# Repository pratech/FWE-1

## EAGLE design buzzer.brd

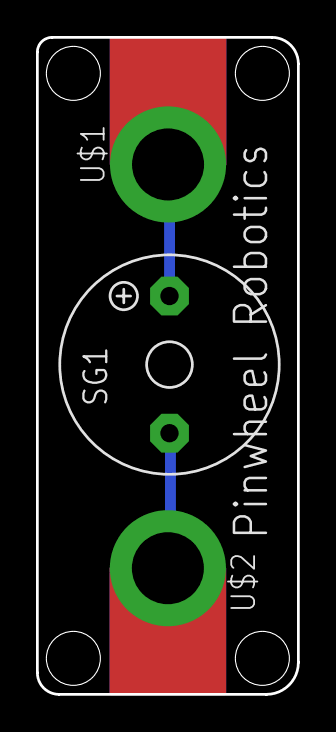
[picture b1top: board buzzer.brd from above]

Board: 2 copper layers, 14.5 x 36.5 mm, 3 parts (0 on the bottom side), 2 nets.

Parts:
SG1: F/TMB
U$1, U$2: MICROBIT_PAD

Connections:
unnamed: SG1.+, U$1.PAD
unnamed: SG1.-, U$2.PAD

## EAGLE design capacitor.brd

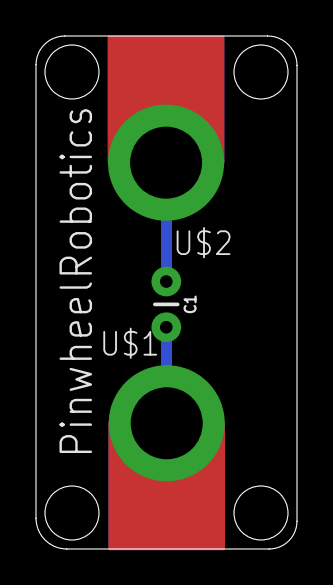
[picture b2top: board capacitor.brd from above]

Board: 2 copper layers, 14.5 x 28.5 mm, 3 parts (0 on the bottom side), 2 nets.

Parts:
C1: 22pF; CAP-PTH-2.54
U$1, U$2: MICROBIT_PAD

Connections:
unnamed: C1.1, U$2.PAD
unnamed: C1.2, U$1.PAD

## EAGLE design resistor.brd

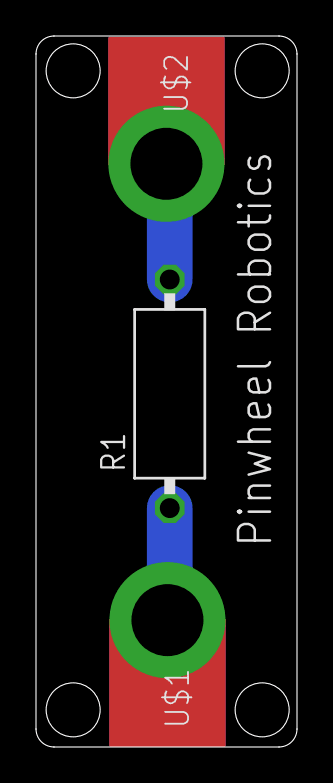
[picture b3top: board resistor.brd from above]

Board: 2 copper layers, 14.5 x 39.5 mm, 3 parts (0 on the bottom side), 2 nets.

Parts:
R1: VMTB60
U$1, U$2: MICROBIT_PAD

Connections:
unnamed: R1.1, U$1.PAD
unnamed: R1.2, U$2.PAD

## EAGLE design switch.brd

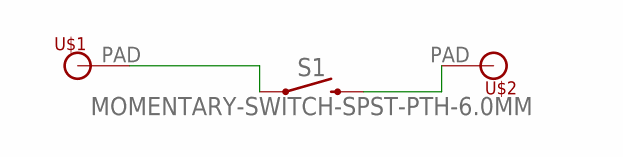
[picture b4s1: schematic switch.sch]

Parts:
S1: MOMENTARY-SWITCH-SPST-PTH-6.0MM; TACTILE_SWITCH_PTH_6.0MM
U$1: pin1; MICROBIT_PAD
U$2: MICROBIT_PAD

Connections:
unnamed: S1.1, U$1.PAD
unnamed: S1.3 (2), U$2.PAD

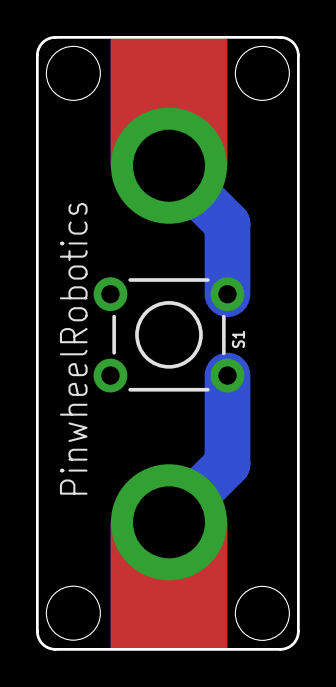
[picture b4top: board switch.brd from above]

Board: 2 copper layers, 14.5 x 34.0 mm, 3 parts (0 on the bottom side), 2 nets.

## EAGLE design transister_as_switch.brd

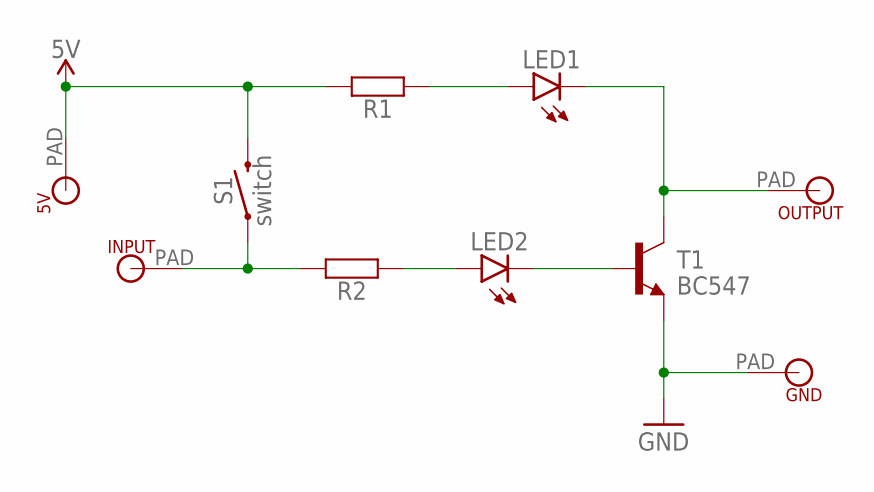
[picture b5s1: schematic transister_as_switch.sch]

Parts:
5V: MICROBIT_PAD
GND: MICROBIT_PAD
INPUT: MICROBIT_PAD
LED1, LED2: LEDCHIP-LED0805; CHIP-LED0805
OUTPUT: MICROBIT_PAD
R1, R2: RESISTOR-07; R0207/7
S1: switch; TACTILE_SWITCH_PTH_6.0MM
T1: BC547; TO92

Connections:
5V: 5V.PAD, R1.2, S1.3 (2)
GND: GND.PAD, T1.1 (E)
unnamed: LED1.C, OUTPUT.PAD, T1.3 (C)
unnamed: LED1.A, R1.1
unnamed: LED2.C, T1.2 (B)
unnamed: LED2.A, R2.1
unnamed: INPUT.PAD, R2.2, S1.1

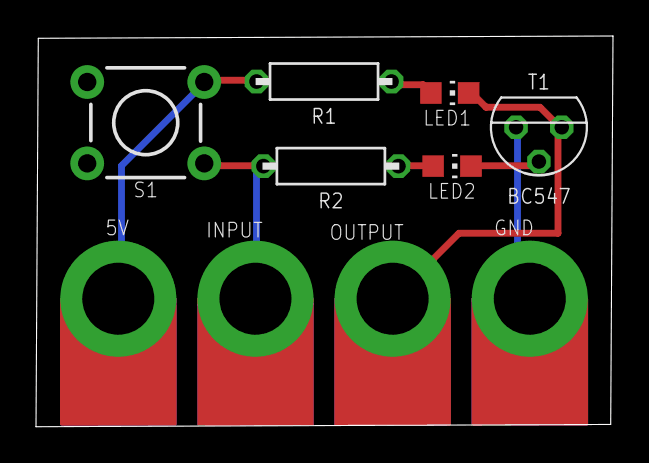
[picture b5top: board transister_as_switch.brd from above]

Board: 2 copper layers, 32.1 x 21.7 mm, 10 parts (0 on the bottom side), 7 nets.

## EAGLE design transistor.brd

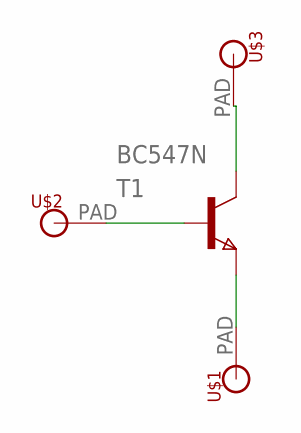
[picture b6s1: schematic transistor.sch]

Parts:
T1: BC547N; TO92
U$1, U$2, U$3: MICROBIT_PAD

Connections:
unnamed: T1.1 (C), U$3.PAD
unnamed: T1.2 (B), U$2.PAD
unnamed: T1.3 (E), U$1.PAD

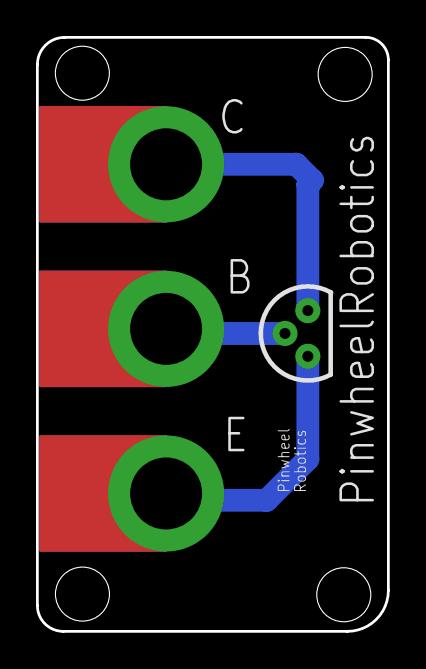
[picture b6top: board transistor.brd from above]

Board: 2 copper layers, 19.5 x 33.0 mm, 4 parts (0 on the bottom side), 3 nets.

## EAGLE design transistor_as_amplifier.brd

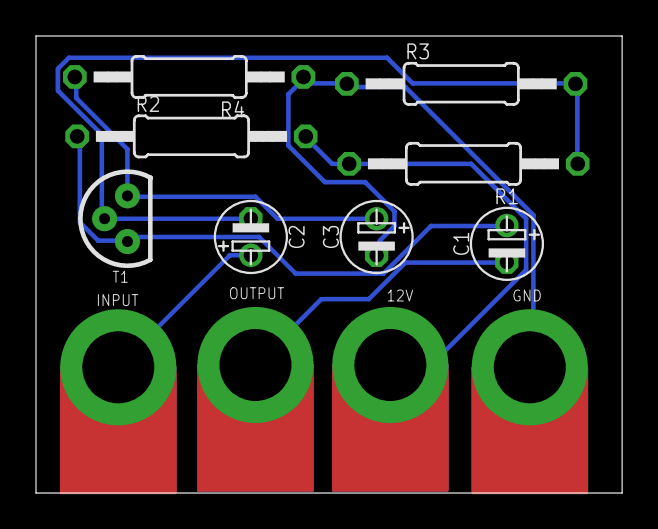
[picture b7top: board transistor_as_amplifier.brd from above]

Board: 2 copper layers, 32.6 x 25.4 mm, 12 parts (0 on the bottom side), 7 nets.

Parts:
12V: MICROBIT_PAD
C1, C2: 10uF; C_E2-4
C3: 47uF; C_E2-4
GND: MICROBIT_PAD
INPUT: MICROBIT_PAD
OUTPUT: MICROBIT_PAD
R1: 100k; 0207/12
R2: 1k; 0207/12
R3: 150K; 0207/12
R4: 470; 0207/12
T1: BC547N; TO92

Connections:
12V: 12V.PAD, R1.2, R2.2
GND: C3.-, GND.PAD, R3.1, R4.1
unnamed: C3.+, R4.2, T1.3
unnamed: C1.+, R2.1, T1.1
unnamed: C2.-, R1.1, R3.2, T1.2
unnamed: C1.-, OUTPUT.PAD
unnamed: C2.+, INPUT.PAD

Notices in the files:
parts and their libraries:
SparkFun-Capacitors: Licensing: Creative Commons ShareAlike 4.0 International - https://creativecommons.org/licenses/by-sa/4.0
